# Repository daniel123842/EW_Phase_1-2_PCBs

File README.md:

# EW_Phase_1-2_PCBs
Repository housing the phase 1 and 2 circuits for RX and TX

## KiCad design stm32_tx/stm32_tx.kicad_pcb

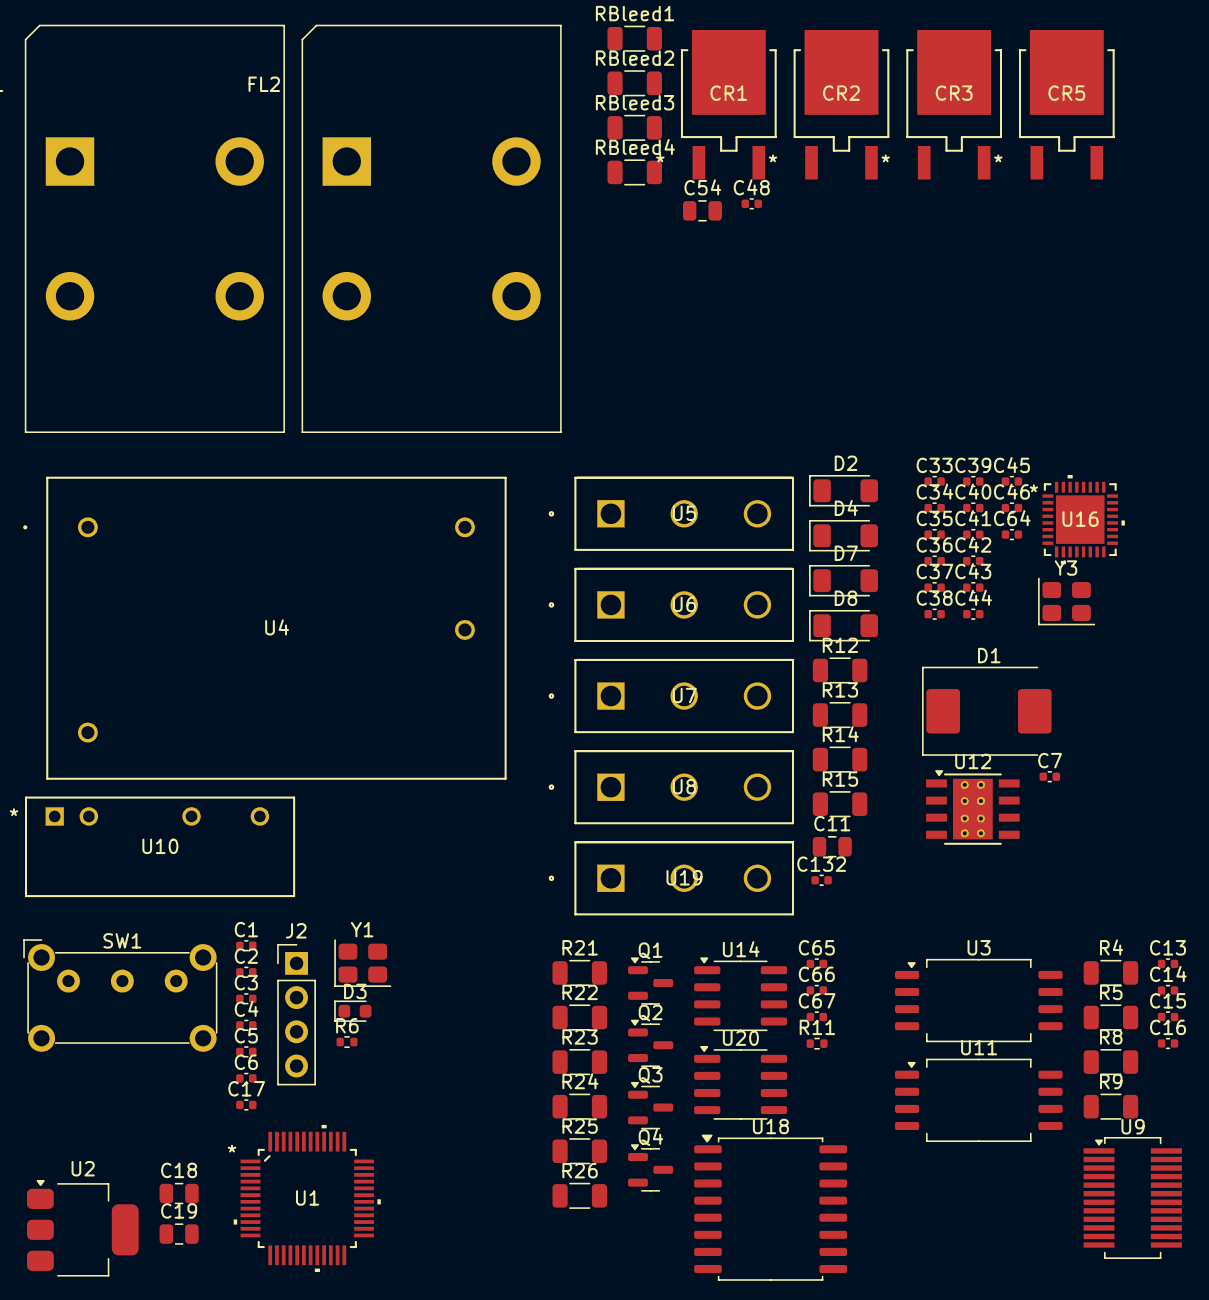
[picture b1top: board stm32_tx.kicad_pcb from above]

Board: 2 copper layers, 93 parts (0 on the bottom side), 68 nets, no tracks yet.

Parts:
C1: 4.7uF; C_0402_1005Metric
C2, C3, C48: 100nF; C_0402_1005Metric
C4: 1uF; C_0402_1005Metric
C5: 100n; C_0402_1005Metric
C6, C17, C34, C35: 10p; C_0402_1005Metric
C7: C; C_0402_1005Metric
C11: 200u; C_0805_2012Metric
C13, C15, C16: 1n; C_0402_1005Metric
C14: 0.1uF; C_0402_1005Metric
C18, C19: 22u; C_0805_2012Metric
C33, C36, C39, C43, C45: 10nF; C_0402_1005Metric
C37, C38, C40, C42, C44, C46, C64: 2.2uF; C_0402_1005Metric
C41: 10uF; C_0402_1005Metric
C54: 470uF; C_0805_2012Metric
C65, C66, C67: 1u; C_0402_1005Metric
C132: 250nF; C_0402_1005Metric
CR1, CR2, CR3, CR5: STPSC10H065B-TR; DPAK_STPS_STM
D1: B340; D_SMC
D2, D4, D7, D8: BZV55B18; D_MiniMELF
D3: LED; LED_0603_1608Metric
FL1, FL2: WE-CMBNC; L_CommonMode_PulseElectronics_PH9455x105NL_1
J2: Conn_01x04_Pin; PinHeader_1x04_P2.54mm_Vertical
Q1, Q2, Q3, Q4: 2N7002; SOT-23
R4, R8, R9: 330k; R_1206_3216Metric
R5, R21, R25: 10k; R_1206_3216Metric
R6, R11: 1k; R_0402_1005Metric
R12, R13, R14, R15: 10; R_1206_3216Metric
R22: 6.2k; R_1206_3216Metric
R23, R24: 1k; R_1206_3216Metric
R26: 4.02k; R_1206_3216Metric
RBleed1, RBleed2, RBleed3, RBleed4: 22k; R_1206_3216Metric
SW1: SW_SPDT; SW_E-Switch_EG1224_SPDT_Angled
U1: STM32G071CBT6; LQFP-48
U2: AMS1117-3.3; SOT-223-3_TabPin2
U3, U11: AMC1351DWV; SOIC-8_7.5x5.85mm_P1.27mm
U4: IRM-01-3.3; IRM02_MWU
U5, U6, U7, U8, U19: IPW65R041CFD7XKSA1; PG-TO247-3-41
U9: ACS709xLFTR-20BB; Allegro_QSOP-24_3.9x8.7mm_P0.635mm
U10: RP-1212S; RP_S_RCP
U12: TPS5430DDA; TI_SO-PowerPAD-8_ThermalVias
U14, U20: TL431D; SOIC-8_3.9x4.9mm_P1.27mm
U16: ST25R3916B-AQWT; VFQFPN32_5X5_WETTABLE_STM
U18: ISO7760DW; SOIC-16W_7.5x10.3mm_P1.27mm
Y1: Crystal1; Crystal_SMD_3225-4Pin_3.2x2.5mm
Y3: 27MHz; Crystal_SMD_3225-4Pin_3.2x2.5mm

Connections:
+5V: C18.1, U2.3 (VI)
+12V_HV: C14.2, C65.1, C67.1, R11.2, R23.2, R24.2, U3.1 (VDD1), U4.12 (+VO), U9.20 (VCC), U10.1 (+VIN), U11.1 (VDD1), U18.16 (Vcc2)
+12V_LV: U10.7 (+VOUT), U12.7 (VIN)
+325V: C11.1, C54.1, CR2.3, CR5.3, RBleed1.1, U5.2 (DRAIN), U7.2 (DRAIN)
/low voltage/MCU/NRST: C6.1, U1.9 (PF1-OSC_OUT), U1.10 (PF2-NRST), Y1.1
/low voltage/MCU/OSC_IN: C17.1, U1.8 (PF0-OSC_IN), Y1.3
/low voltage/MCU/SWDIO: J2.2, U1.35 (PA13)
/low voltage/MCU/SYSCLK: J2.3, SW1.2 (B), U1.36 (PA14-BOOT0)
BUCK_EN: U1.23 (PB11), U12.5 (EN)
COIL_VOLTAGE: R5.1, R9.2, U11.2 (IN)
COUT+: U1.26 (PB14), U3.7 (OUTP)
COUT-: U1.27 (PB15), U3.6 (OUTN)
GND_A: C1.2, C2.2, C3.2, C4.2, C5.2, C6.2, C17.2, C18.2, C19.2, C33.2, C34.2, C35.2, C36.2, C37.2, C38.2, C39.2, C40.2, C41.2, C42.2, C43.2, C44.2, C45.2, C46.2, C64.2, D1.2 (A), J2.4, R6.1, SW1.1 (A), U1.7 (VSS), U2.1 (GND), U3.5 (GND2), U10.5 (-VOUT), U11.5 (GND2), U12.6 (GND), U12.9 (GNDPAD), U16.6 (GND_D), U16.12 (GND_DR1), U16.14 (VDD_DR), U16.16 (GND_DR2), U16.20 (I2C_EN), U16.21 (VSS), U16.22 (RFI1), U16.26 (GND_A), U16.33 (GND), U18.8 (GND1), Y1.2, Y1.4, Y3.2, Y3.4
GND_HV: C11.2, C13.1, C14.1, C15.1, C16.1, C54.2, C65.2, C67.2, CR1.2, CR3.2, D7.1 (K), D8.1 (K), Q1.2 (S), Q2.2 (S), Q3.2 (S), Q4.2 (S), R5.2, R21.2, R25.2, RBleed4.2, U3.3 (GND1), U3.4 (GND1), U4.13 (-VO), U6.3 (SOURCE), U8.3 (SOURCE), U9.15 (GND), U10.2 (-VIN), U11.3 (GND1), U11.4 (GND1), U14.2 (A), U14.3 (A), U14.6 (A), U14.7 (A), U18.9 (GND2), U19.3 (SOURCE), U20.2 (A), U20.3 (A), U20.6 (A), U20.7 (A)
HIN1: Q4.3 (D), U18.15 (OUTA)
HIN2: Q2.3 (D), U18.13 (OUTC)
IRQ: U1.43 (PB4), U16.27 (IRQ)
LIN1: Q3.3 (D), U18.14 (OUTB)
LIN2: Q1.3 (D), U18.12 (OUTD)
LINE_FL: C48.1, CR1.3, CR5.2
MAINS_NEUTRAL: FL1.2, U4.24 (AC/N)
NEUTRAL_FL: C48.2, CR2.2, CR3.3, FL2.3
unnamed: FL1.4, FL2.1
unnamed: FL1.3, FL2.2
unnamed: C7.2, D1.1 (K), U12.8 (PH)
unnamed: D2.2 (A), R14.2, U7.1 (GATE)
unnamed: D3.1 (K), R6.2
unnamed: D4.2 (A), R12.2, U5.1 (GATE)
unnamed: D7.2 (A), R13.2, U6.1 (GATE)
unnamed: D8.2 (A), R15.2, U8.1 (GATE)
unnamed: R4.2, R8.1
unnamed: R8.2, R9.1
unnamed: RBleed1.2, RBleed2.1
unnamed: RBleed2.2, RBleed3.1
unnamed: RBleed3.2, RBleed4.1
unnamed: C16.2, U9.17 (FILTER)
unnamed: C15.2, U9.16 (VZCR)
unnamed: C13.2, U9.19 (~FAULT)
unnamed: C7.1, U12.1 (BOOT)
unnamed: R11.1, R22.1, U14.1 (K)
unnamed: R24.1, R26.1, U20.1 (K)
unnamed: R21.1, R22.2, U14.8 (REF)
unnamed: C36.1, C37.1, U16.24 (AGDC)
unnamed: C33.1, C38.1, U16.3 (VDD_D)
unnamed: R25.1, R26.2, U20.8 (REF)
OVC: Q1.1 (G), Q2.1 (G), Q3.1 (G), Q4.1 (G), R23.1, U19.1 (GATE)
PA0: U1.11 (PA0), U18.2 (INA)
PA1: U1.12 (PA1), U18.3 (INB)
PA2: U1.13 (PA2), U18.4 (INC)
PA3: U1.14 (PA3), U18.5 (IND)
SPI_MISO: U1.20 (PB1), U16.32 (MISO/SDA)
SPI_MOSI: U1.19 (PB0), U16.31 (MOSI)
SPI_NSS: U1.42 (PB3), U16.29 (BSS)
SPI_SCK: U1.21 (PB2), U16.30 (SCLK/SCL)
TX_CIOUT: U3.2 (IN), U9.18 (VIOUT)
TX_FAULT_EN: U1.16 (PA5), U9.22 (FAULT_EN)
TX_IP+: U9.1 (IP+), U9.2 (IP+), U9.3 (IP+), U9.4 (IP+), U9.5 (IP+), U9.6 (IP+)
TX_IP-: C66.2, D2.1 (K), U7.3 (SOURCE), U8.2 (DRAIN), U9.7 (IP-), U9.8 (IP-), U9.9 (IP-), U9.10 (IP-), U9.11 (IP-), U9.12 (IP-)
TX_VCOIL: C132.2, R4.1
VDD: C1.1, C2.1, C3.1, C4.1, C19.1, C41.1, C42.1, C43.1, C44.1, D3.2 (A), J2.1, SW1.3 (C), U1.4 (VBAT), U1.5 (VREF+), U1.6 (VDD), U2.2 (VO), U3.8 (VDD2), U11.8 (VDD2), U16.1 (VDD_IO), U16.8 (VDD), U16.10 (VDD_TX), U18.1 (Vcc1)
VDD_A: C39.1, C40.1, U16.7 (VDD_A)
VDD_AM: C64.1, U16.11 (VDD_AM)
VDD_RF: C45.1, C46.1, U16.9 (VDD_RF)
VOUT+: U1.24 (PB12), U11.7 (OUTP)
VOUT-: U1.25 (PB13), U11.6 (OUTN)
VS_left: C132.1, D4.1 (K), U5.3 (SOURCE), U6.2 (DRAIN)
XTI: C35.1, U16.5 (XTI), Y3.3
XTO: C34.1, U16.4 (XTO), Y3.1
